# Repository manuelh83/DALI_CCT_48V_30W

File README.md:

# DALI CCT 48V 30W

DALI-2 DT8 Tunable White LED driver reference design für **48 V DC SELV Eingang** mit bis zu **30 W LED-Leistung**.

Dieses Repository enthält **Hardware- und Firmware-Umfang** inklusive Dokumentation für Entwicklung, Bring-up, Test und Inbetriebnahme.

> ⚠️ **Wichtig:** Referenzdesign für Entwicklungs- und Evaluierungszwecke. Kein automatisch zertifiziertes Endprodukt.

---

## Inhaltsübersicht

- [Projektüberblick](#projektüberblick)
- [Systemarchitektur](#systemarchitektur)
- [Repository-Struktur](#repository-struktur)
- [Hardware-Umfang](#hardware-umfang)
- [Software/Firmware-Umfang](#softwarefirmware-umfang)
- [Toolchain & Voraussetzungen](#toolchain--voraussetzungen)
- [Build & Flash (Firmware)](#build--flash-firmware)
- [Inbetriebnahme (HowTo)](#inbetriebnahme-howto)
- [Test & Verifikation](#test--verifikation)
- [Troubleshooting](#troubleshooting)
- [Sicherheitshinweise](#sicherheitshinweise)
- [Weiterführende Dokumentation](#weiterführende-dokumentation)

---

## Projektüberblick

Das Design realisiert einen DALI-2 DT8 CCT-Treiber (Tunable White) mit:

- **Eingang:** 48 V DC SELV (typischer Bereich 43.2–52.8 V)
- **Ausgang:** gemeinsamer Anodenbus `LED+` und zwei geregelte Kanäle `WW−` / `CW−`
- **Leistung:** bis 30 W
- **Regelung:** kontinuierliche analoge Stromdimmung (0.1–100 %, ohne niederfrequentes PWM-Flackern)
- **Kommunikation:** galvanisch isolierte DALI-2 DT8 Tc Schnittstelle
- **Steuerung:** STM32G031K8T6 + AT24C32E EEPROM

Ziel ist ein robustes Referenzsystem, das als Grundlage für eigene Leuchten-/Treiberentwicklungen dient.

---

## Systemarchitektur

1. **Primärversorgung / Eingangsseite**
   - 48 V SELV Versorgung mit Schutzkonzept für Überspannungsereignisse.

2. **Leistungsteil**
   - 4‑Switch synchroner Buck-Boost (LT8390A) erzeugt geregelten LED-Bus.

3. **LED-Kanalregelung**
   - Zwei lineare Low-Side Konstantstromsenken für Warmweiß/Kaltweiß.

4. **Steuer- und Kommunikationsschicht**
   - STM32G0 übernimmt DALI-Stack, DT8-Verhalten, Kanalmischung, Schutzreaktionen und Persistenz.

5. **Nichtflüchtige Datenhaltung**
   - Externes EEPROM für Parameter, Zustände und Konfigurationswerte.

---

## Repository-Struktur

```text
.
├─ .github/
├─ README.md
├─ firmware/
│  ├─ README.md
│  ├─ docs/
│  │  ├─ README.md
│  │  ├─ build.md
│  │  ├─ api.md
│  │  ├─ dali_implementation.md
│  │  └─ troubleshooting.md
│  ├─ src/
│  ├─ test/
│  └─ lib/
└─ hardware/
   └─ DALI_CCT_48V_30W/
      ├─ README.md
      └─ docs/
         ├─ design-specification.md
         ├─ bom.csv
         ├─ net-class-and-layout-rules.md
         ├─ bring-up-and-test-plan.md
         ├─ open-items-and-risks.md
         └─ firmware-interface.md
```

> Die exakte Dateiliste kann sich weiterentwickeln; für die aktuelle Struktur bitte das Repository-Browsing verwenden.

---

## Hardware-Umfang

Im Pfad `hardware/DALI_CCT_48V_30W/` liegt das vollständige Hardware-Referenzprojekt mit:

- KiCad-Projektdateien (4-Layer PCB, 150 × 60 mm)
- BOM mit Bauteilauswahl und Alternativen
- Spezifikation, Layout-/Netzklassenregeln
- Bring-up-/Testplan
- Risiken & offene Punkte
- Schnittstellendokument zur Firmware-Anbindung

Kernmerkmale:

- 48 V DC SELV Eingang
- 30 W Ausgangsleistung
- gemeinsamer LED+ Bus, getrennte WW/CW Senken
- analoge, kontinuierliche Stromdimmung
- isolierte DALI-2 DT8 Schnittstelle

---

## Software/Firmware-Umfang

Im Pfad `firmware/` befindet sich eine produktionsorientierte Firmware-Basis für **STM32G031** plus host-testbare Logik.

### Enthaltene Bereiche

- `firmware/src/`
  - Hardwareabstraktion/HAL-Wrapper
  - DALI-Kommunikations- und Auswertepfade
  - CCT-/Kanalregel- und Schutzlogik
  - NVM-Zugriffe (EEPROM)
  - Scheduler/Task-Orchestrierung

- `firmware/test/`
  - Host-seitige Unit-Tests für zentrale Protokoll-/Regellogik

- `firmware/docs/`
  - `build.md` (Build/Flash)
  - `api.md` (Modul-/API-Überblick)
  - `dali_implementation.md` (DT8-Verhalten)
  - `troubleshooting.md` (Fehlersuche)

- `firmware/lib/`
  - Integrationshaken für STM32CubeG0 bzw. plattformnahe Komponenten

### Firmware-Funktionsumfang (auf hoher Ebene)

- DALI-2/DT8 Kommandopfad
- Helligkeits- und CCT-bezogene Sollwertverarbeitung
- Kanalmischung WW/CW gemäß Zieltemperatur/Farbanteil
- Schutz- und Fehlerbehandlung (z. B. Grenzwertverletzungen)
- Persistenz relevanter Parameter im EEPROM

---

## Toolchain & Voraussetzungen

### Hardware

- Labornetzteil 48 V DC mit Strombegrenzung
- Last (geeignetes CCT-LED-Setup)
- DALI-Master / DALI-USB Interface
- Multimeter, optional Oszilloskop und Thermalkamera

### Software/Firmware

- ARM GCC Toolchain (oder projektspezifisch dokumentierte Alternative)
- Build-System gemäß `firmware/docs/build.md`
- Flash/Debug-Tool für STM32G0
- Optional: Host-Testumgebung (Compiler + Testframework laut `firmware/test`)

---

## Build & Flash (Firmware)

> Verbindliche Details stehen in `firmware/docs/build.md`.

Typischer Ablauf:

1. Toolchain installieren
2. Firmware-Projekt konfigurieren
3. Build erzeugen (Debug/Release)
4. Binary/ELF auf STM32G031 flashen
5. Serielles Logging / Debug-Schnittstelle prüfen
6. Basisfunktion ohne DALI-Verkehr verifizieren

Empfehlung:

- Erst mit konservativen Strom-/Leistungsgrenzen testen
- Schutzpfade und Fault-Indikationen früh validieren

---

## Inbetriebnahme (HowTo)

Diese Schrittfolge ist als praxisorientierter Leitfaden gedacht und ergänzt den detaillierten Bring-up-Plan unter `hardware/.../docs/bring-up-and-test-plan.md`.

### 1) Sichtprüfung (ohne Spannung)

- Bestückung, Polaritäten, Lötqualität, Steckverbinder prüfen
- Isolations- und Kriechstrecken visuell kontrollieren
- Sicherstellen, dass keine Kurzschlüsse zwischen kritischen Netzen vorliegen

### 2) Erstes Einschalten (ohne LED-Last)

- Labornetzteil auf 48 V setzen, Stromlimit niedrig starten
- Board versorgen und Ruhestrom plausibilisieren
- Grundversorgungen (MCU-Rails, Referenzen) messen

### 3) Firmware laden und Basiskommunikation testen

- Firmware flashen
- MCU startet ohne Fault-Latch
- Debug/Statusausgaben oder definierte Lebenszeichen prüfen

### 4) DALI-Bus anbinden

- DALI-Leitungen korrekt verbinden (Polarität/Buskonzept beachten)
- DALI-Master verbinden
- Erreichbarkeit und Reaktion auf Basisbefehle verifizieren

### 5) LED-Last anschließen

- CCT-Last korrekt an `LED+`, `WW−`, `CW−` anschließen
- Mit niedrigen Sollwerten starten
- Kanalströme messen und plausibilisieren

### 6) Funktionsprüfung CCT/Helligkeit

- Helligkeitsrampe über den vorgesehenen Bereich prüfen
- CCT-Änderungen (warm ↔ kalt) beobachten
- Übergänge auf Stabilität/Flickerfreiheit prüfen

### 7) Schutz- und Grenzfalltests

- Grenzbereiche in kontrollierter Form anfahren
- Verifikation von Fault-Reaktionen und Recovery-Strategie
- Sicherstellen, dass keine unzulässige Überlastung entsteht

### 8) Thermik-Check unter Dauerlast

- Erwärmung an kritischen Komponenten überwachen
- Betriebspunkt nur freigeben, wenn thermisch stabil

### 9) Persistenz/NVM prüfen

- Relevante Parameter ändern
- Power-Cycle durchführen
- Wiederherstellung aus EEPROM verifizieren

### 10) Abschlussfreigabe (Prototyp)

- Dokumentierte Sollwerte/Abnahmekriterien abgleichen
- Messergebnisse protokollieren

---

## Test & Verifikation

Empfohlene Reihenfolge:

1. Host-Unit-Tests (`firmware/test`)
2. Kommunikationspfad DALI/DT8
3. Kanalregelung und CCT-Verhalten
4. Fault-Injection / Schutzpfade
5. Thermik- und Dauerlasttests

Für formale Kriterien den hardwareseitigen Bring-up/Testplan verwenden.

---

## Troubleshooting

- Kein Start nach Flash:
  - Takt-/Reset-Konfiguration und Build-Target prüfen
  - Versorgung und Brownout-Bedingungen verifizieren

- DALI ohne Reaktion:
  - Busverdrahtung und Master-Konfiguration kontrollieren
  - Implementierte DT8-Kommandos mit `firmware/docs/dali_implementation.md` abgleichen

- Instabiles Dimmverhalten:
  - Sollwertgrenzen und Kalibrierungen prüfen
  - Kanalströme und Lastkompatibilität messen

- Unerwartete Faults:
  - Schutzschwellen/Telemetrie sichten
  - Schritte aus `firmware/docs/troubleshooting.md` anwenden

---

## Sicherheitshinweise

- Nur durch qualifiziertes Fachpersonal in geeigneter Laborumgebung betreiben
- Strombegrenzung beim Erststart immer aktivieren
- Thermische Risiken bei Dauerlast berücksichtigen
- Isolations- und EMV-Anforderungen für Zielprodukt separat validieren

---

## Weiterführende Dokumentation

### Root

- `README.md` (dieses Dokument)

### Hardware

- `hardware/DALI_CCT_48V_30W/README.md`
- `hardware/DALI_CCT_48V_30W/docs/design-specification.md`
- `hardware/DALI_CCT_48V_30W/docs/bom.csv`
- `hardware/DALI_CCT_48V_30W/docs/net-class-and-layout-rules.md`
- `hardware/DALI_CCT_48V_30W/docs/bring-up-and-test-plan.md`
- `hardware/DALI_CCT_48V_30W/docs/open-items-and-risks.md`
- `hardware/DALI_CCT_48V_30W/docs/firmware-interface.md`

### Firmware

- `firmware/README.md`
- `firmware/docs/README.md`
- `firmware/docs/build.md`
- `firmware/docs/api.md`
- `firmware/docs/dali_implementation.md`
- `firmware/docs/troubleshooting.md`

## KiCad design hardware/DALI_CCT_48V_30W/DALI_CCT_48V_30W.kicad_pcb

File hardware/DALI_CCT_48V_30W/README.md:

# DALI CCT 48V 30W – Hardware Reference Design Rev A

> **⚠️ WARNING – REFERENCE DESIGN ONLY**
>
> This is an engineering reference design. It **must not be manufactured or deployed** without:
> - Independent schematic review and simulation
> - Prototype build and validation
> - Thermal design verification
> - EMC testing per applicable standards (e.g., EN 55015 / CISPR 15)
> - Electrical safety assessment (e.g., IEC 62368-1 / EN 61347-2-13)
> - DALI-2 conformance testing (DIIA/DALI Alliance test suites)
> - All applicable regulatory approvals for target market

---

## Project Scope

A production-oriented KiCad 8+ reference design for a **48 V SELV, 30 W maximum, DALI-2 DT8 Tunable White LED driver** with the following key features:

| Parameter | Value |
|---|---|
| Input voltage | 48 V DC SELV, operating range 43.2–52.8 V |
| Transient protection | Designed for short transients up to 60 V |
| LED output | 30 W max total; three terminals LED+, WW−, CW− (common-anode CCT) |
| LED string range | 28–42 V per channel |
| Max current per channel | 700 mA (firmware limits total power to ≤30 W) |
| Dimming | 0.1–100%, continuous/analog current control, no low-frequency PWM |
| DALI | DALI-2 control gear, DT8 Tc Tunable White (IEC 62386-101/-102/-209) |
| PCB size | 150 × 60 mm, 4 layers |
| Component height | ≤30 mm |
| Thermal | Aluminium enclosure coupling via B.Cu thermal zone + thermal vias |

---

## Architecture

```
48V DC SELV IN
    │
    ├── [J1] 48V_IN+/48V_IN− screw terminal (5.08mm)
    │
    ├── BLOCK 1: Input Protection
    │     F1: Fuse 1A slow-blow
    │     D1: P-channel MOSFET reverse-polarity protection
    │     TV1: TVS 60V/600W bidirectional clamp
    │     C1,C2: 100µF/63V bulk caps + EMI filter
    │
    ├── BLOCK 4: Auxiliary Supply 48V→5V→3.3V
    │     U_AUX1: LMR16006YDDAR synchronous buck (5V/600mA)
    │     U_LDO: AP2112K-3.3 LDO (3.3V/600mA)
    │
    ├── BLOCK 2: 4-Switch Synchronous Buck-Boost LED Bus
    │     U_BB: LT8390A controller, Q1-Q4 MOSFETs, L2 47µH
    │     Output: LED_BUS+ nominally 44V
    │     → [J3-pin1] LED+ (common anode)
    │
    ├── BLOCK 3: Two Linear Low-Side Current Sinks
    │     Q_WW + R_SENSE_WW + U_CS_WW (OPA2333) → [J3-pin2] WW−
    │     Q_CW + R_SENSE_CW + U_CS_CW (OPA2333) → [J3-pin3] CW−
    │     Hardware OCP via LM393 comparator (threshold ~900mA)
    │     Analog current setpoint from MCU DAC (MCP4728 12-bit I2C)
    │
    ├── BLOCK 5: MCU, NVM, SWD
    │     U_MCU: STM32G031K8T6 (ARM Cortex-M0+, 64KB flash)
    │     U_EEP: AT24C32E I2C EEPROM (DALI NVM)
    │     U_DAC: MCP4728 12-bit quad DAC (current setpoints)
    │     [J4] SWD programming header (1.27mm)
    │
    └── BLOCK 6: Galvanically Isolated DALI Interface
          Isolation goal: 2.5kVrms (subject to safety standard review)
          U_DALI: NXP UBA2015 or optocoupler-based frontend
          D_ESD: PRTR5V0U2X ESD protection
          [J2] DALI_A/DALI_B screw terminal (5.08mm)
```

### Power Architecture Note

This design uses a **common regulated 4-switch synchronous buck-boost LED bus** (nominally 44 V) followed by **two independently controlled, linear low-side constant-current sinks** (WW and CW). This is the correct representation: a single regulated voltage bus with common LED anode, and individual current control on the low side per channel.

---

## Opening in KiCad 8+

1. Open KiCad 8.0 or later.
2. File → Open Project → select `DALI_CCT_48V_30W.kicad_pro`.
3. Open the schematic editor: `DALI_CCT_48V_30W.kicad_sch`.
4. Open the PCB editor: `DALI_CCT_48V_30W.kicad_pcb`.

### ERC/DRC Status (Rev A.1)

**Schematic (`.kicad_sch`):** All KiCad symbol instances required for the current reference design are present, and U_BB now uses the exact project-local `AnalogDevices:LT8390AIFE` 28-pin symbol instead of the generic `Device:IC`. The schematic netlist is still intended to be verified with KiCad 8 ERC after opening the project locally. See OI-011 in `docs/open-items-and-risks.md` for full details.

**PCB (`.kicad_pcb`):**
- Board outline, mounting holes, and connector footprints defined (Rev A)
- **Rev A.1 additions**: D2PAK footprints for Q_WW and Q_CW with 9 thermal vias each and 20×20mm B.Cu thermal pour zones
- Isolation barrier silkscreen updated: `ISO BARRIER: CLR>=2mm / CRG>=5mm / ZONE=8mm (IEC 62368-1:2018)`
- Full component placement and routing requires KiCad 8 GUI after netlist import from schematic

**Intentional open items / known DRC status:**
- Routing is incomplete; ratsnest will show unconnected nets after netlist import
- Q_WW/Q_CW D2PAK gate pads are unconnected pending netlist import (expected)
- Other complex ICs still use generic `Device:IC` symbols — replace them with exact library symbols in follow-up cleanup work
- Full DRC pass (including creepage/clearance checks for `DALI_ISO` net class) requires complete routing

**Normative DRC rules (`.kicad_dru`):**
- `DALI_ISO` class: clearance ≥ 2.0mm (IEC 62368-1:2018 Table G.8), keepout zone ≥ 8mm (satisfies creepage ≥ 5.0mm with margin)
- `PWR_HV` (48V): clearance ≥ 0.5mm, track width ≥ 2.0mm
- `PWR_LED` (LED bus): track width ≥ 1.5mm
- `KELVIN` (sense): track width ≤ 0.2mm, Kelvin-pair routing required

See `docs/open-items-and-risks.md` for full list of open items (OI-011: RESOLVED, OI-012: IN PROGRESS).

---

## Directory Structure

```
hardware/DALI_CCT_48V_30W/
├── DALI_CCT_48V_30W.kicad_pro      KiCad 8 project file
├── DALI_CCT_48V_30W.kicad_sch      Schematic (functional block descriptions + net list)
├── DALI_CCT_48V_30W.kicad_pcb      PCB layout (board outline, layer setup, key placements)
├── README.md                        This file
└── docs/
    ├── design-specification.md      Full electrical specification
    ├── bom.csv                      Bill of Materials
    ├── net-class-and-layout-rules.md  PCB routing rules and net classes
    ├── bring-up-and-test-plan.md    Prototype bring-up sequence
    ├── open-items-and-risks.md      Open design items and risks
    └── firmware-interface.md        MCU/firmware interface documentation
```

---

## Practical Power and Current Limits

| Condition | WW Current | CW Current | Total Power |
|---|---|---|---|
| Full warm white (2700K) | 700 mA | 0 mA | ≤28 W at 40V LED |
| Full cool white (6500K) | 0 mA | 700 mA | ≤28 W at 40V LED |
| Neutral white (4000K) | ~350 mA | ~350 mA | ≤25 W typical |
| Firmware hard limit | | | 30 W total |
| Hardware OCP per channel | 1.05 A | 1.05 A | — |

The firmware enforces `P_total = V_LED_BUS × (I_WW + I_CW) ≤ 30 W` using ADC-measured bus voltage and DAC-controlled current.

---

## License / Disclaimer

This reference design is provided as-is for engineering reference purposes only. No warranty of fitness for any purpose is expressed or implied. The designer and contributors accept no liability for any direct or indirect damages arising from use of this material. All component datasheets, safety standards, and certification requirements must be independently verified by a qualified engineer before manufacture.

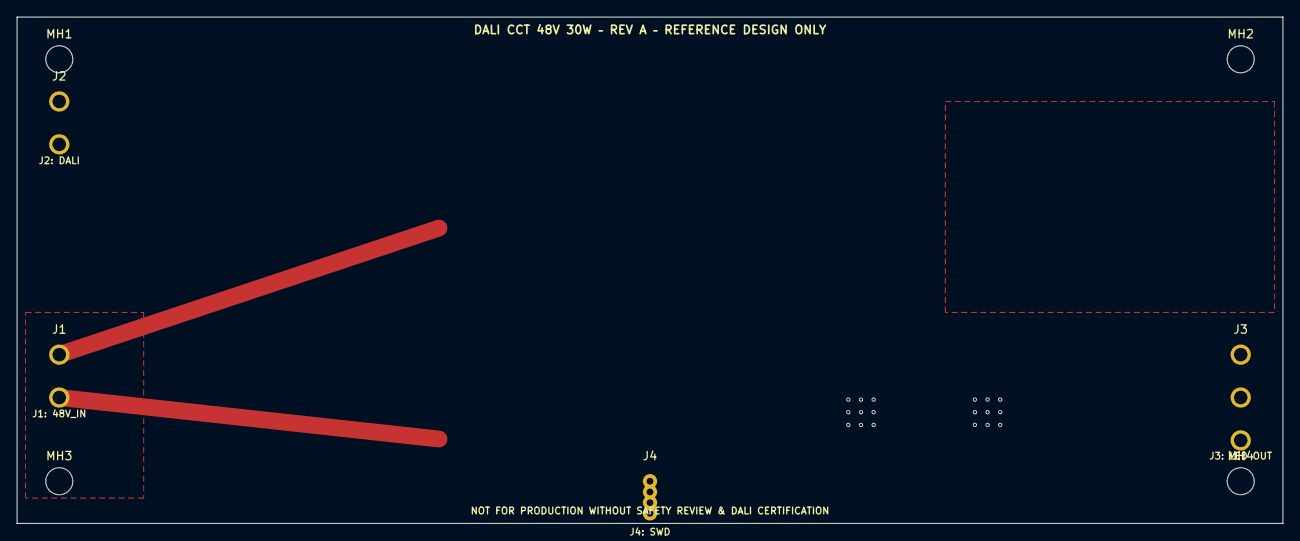
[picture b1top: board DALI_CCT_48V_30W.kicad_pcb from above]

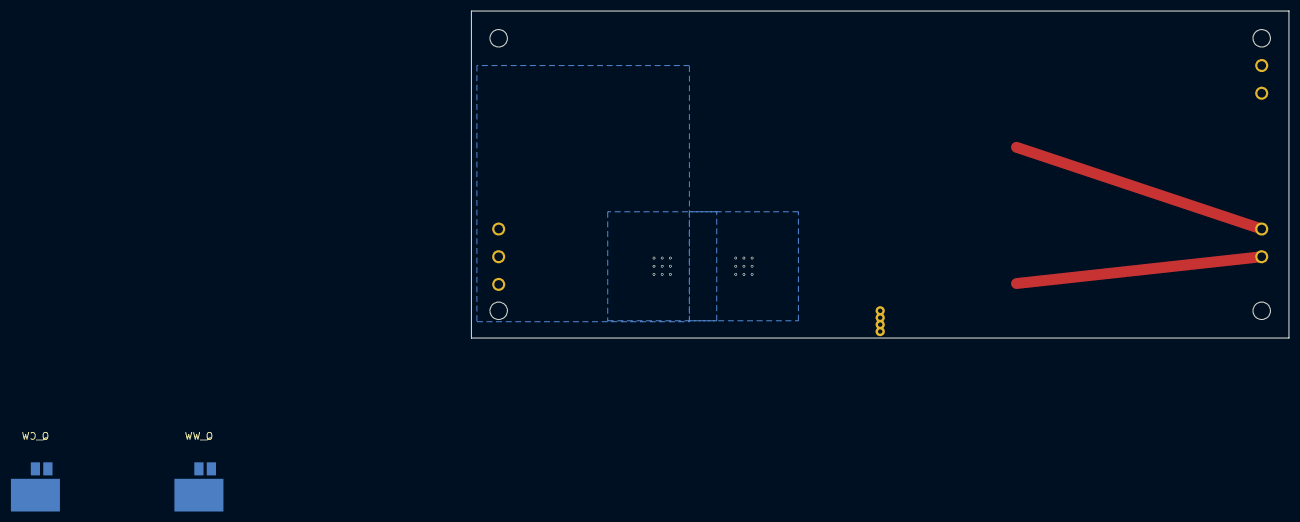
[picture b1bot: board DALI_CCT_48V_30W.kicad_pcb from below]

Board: 4 copper layers, 150.0 x 60.0 mm, 10 parts (2 on the bottom side), 3 nets.

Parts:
J1: 48V_IN 5.08mm; PinHeader_1x02_P2.54mm_Vertical
J2: DALI 5.08mm; PinHeader_1x02_P2.54mm_Vertical
J3: LED 5.08mm; PinHeader_1x03_P2.54mm_Vertical
J4: SWD 1.27mm; PinHeader_1x04_P1.27mm_Vertical
MH1, MH2, MH3, MH4: MountingHole; MountingHole_3.2mm_M3
Q_CW: STB20NF06L D2PAK 60V/20A Rth_jc=3.1°C/W; TO-263-3_TabDown
Q_WW: STB20NF06L D2PAK 60V/20A Rth_jc=3.1°C/W; TO-263-3_TabDown

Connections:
CW-: J3.3, Q_CW.3
PGND: J1.2, J4.1, Q_CW.2, Q_WW.2
WW-: J3.2, Q_WW.3
